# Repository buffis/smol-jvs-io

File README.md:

# smol-jvs-io

Smol JVS IO is a scoped down JVS I/O board designed to work as a drop-in replacement for arcade stick PCB's, to allow them to interface with JVS hardware. It is not meant to function as a fully functional JVS IO in terms of functionality.

This hardware and software of this board was forked from [td-io](https://github.com/tdaede/td-io) and then heavily scoped down to fit my needs. The td-io firmware is not directly compatible, due to design shortcuts on this board such as removing the shift registers.

At this point, I suppose not much of the td-io hardware schematic is used here any more. The firmware is still a pretty close fork though.

# Features

* JVS IO board interface as one-player device.
* Brook board compatible 20pin connector for hooking up player 1 stick and buttons.
* Upgradeable firmware

# BOM

Note that earlier versions may miss some of these, or have other component identifiers, but overall should be the same.

- U1 ADM3485EARZ-REEL7 or ST3485EBDR (or some other pin compatible one)
- U2 Raspberry Pi Pico
- Q1 AO3400A (Or any similar mosfet)
- D1 BAV99S,115 
- R1 0805 120ohm
- R2 0805 1k ohm
- J1 USBR-B-S-F-O-TH (Digikey: SAM10873-ND)
- J2 JST PH 1x4
- J3 JST PH 1x4
- J4 2.54mm Pinheader 2x10
- J5 JST XH 1x2

# Stuff intentionally not provided

* Player 2 controls
* Chaining other JVS IO boards
* Video/Audio handling
* Analog controls, Mahjong controls...

# Power

Power can either be provided to the micro USB port of the raspberry pi pico, or through the +5V/GND pins of the board.

# Firmware Updates

Flash the Raspberry Pi Pico with new firmware. Make sure stick is not powered from other sources.

# License

CERN-OHL-W

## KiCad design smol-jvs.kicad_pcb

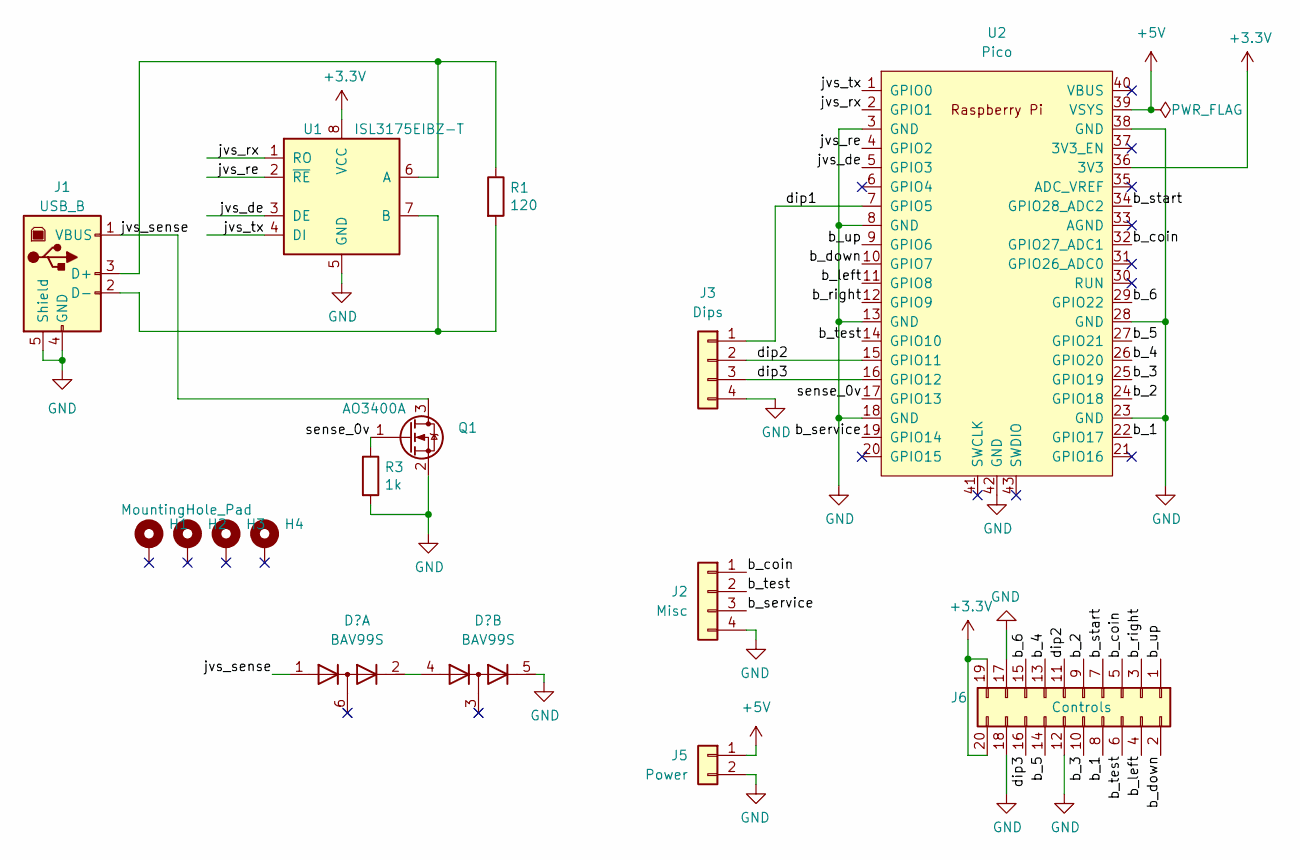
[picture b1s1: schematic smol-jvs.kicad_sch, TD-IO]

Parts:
H1, H2, H3, H4: MountingHole_Pad; MountingHole_2.5mm_Pad
J1: USB_B; USB_B_OST_USB-B1HSxx_Horizontal; Digikey SAM10873-ND
J2: Misc; JST_PH_B4B-PH-K_1x04_P2.00mm_Vertical
J3: Dips; JST_PH_B4B-PH-K_1x04_P2.00mm_Vertical
J5: Power; JST_XH_B2B-XH-AM_1x02_P2.50mm_Vertical
J6: Controls; PinHeader_2x10_P2.54mm_Vertical
Q1: AO3400A; SOT-23
R1: 120; R_0805_2012Metric; Digikey 13-RT0805FRE07120RLCT-ND
R3: 1k; R_0805_2012Metric; Digikey 311-10.0KCRCT-ND
U1: ISL3175EIBZ-T; SOIC-8_3.9x4.9mm_P1.27mm; Digikey 1016-1150-5-ND
U2: Pico; RPi_Pico_SMD_TH

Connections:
+3V3: J6.19, J6.20, U1.8 (VCC), U2.36 (3V3)
+5V: J5.1, U2.39 (VSYS)
/b_1: J6.8, U2.22 (GPIO17)
/b_2: J6.9, U2.24 (GPIO18)
/b_3: J6.10, U2.25 (GPIO19)
/b_4: J6.13, U2.26 (GPIO20)
/b_5: J6.14, U2.27 (GPIO21)
/b_6: J6.15, U2.29 (GPIO22)
/b_coin: J2.1, J6.5, U2.32 (GPIO27_ADC1)
/b_down: J6.2, U2.10 (GPIO7)
/b_left: J6.4, U2.11 (GPIO8)
/b_right: J6.3, U2.12 (GPIO9)
/b_service: J2.3, U2.19 (GPIO14)
/b_start: J6.7, U2.34 (GPIO28_ADC2)
/b_test: J2.2, J6.6, U2.14 (GPIO10)
/b_up: J6.1, U2.9 (GPIO6)
/dip1: J3.1, U2.7 (GPIO5)
/dip2: J3.2, J6.11, U2.15 (GPIO11)
/dip3: J3.3, J6.16, U2.16 (GPIO12)
/jvs_de: U1.3 (DE), U2.5 (GPIO3)
/jvs_re: U1.2 (~RE), U2.4 (GPIO2)
/jvs_rx: U1.1 (RO), U2.2 (GPIO1)
/jvs_sense: J1.1 (VBUS), Q1.3 (D); also elsewhere on the board
/jvs_tx: U1.4 (DI), U2.1 (GPIO0)
/sense_0v: Q1.1 (G), R3.1, U2.17 (GPIO13)
GND: J1.4 (GND), J1.5 (Shield), J2.4, J3.4, J5.2, J6.12, J6.17, J6.18, Q1.2 (S), R3.2, U1.5 (GND), U2.3 (GND), U2.8 (GND), U2.13 (GND), U2.18 (GND), U2.23 (GND), U2.28 (GND), U2.38 (GND), U2.42 (GND); also elsewhere on the board
unnamed: J1.2 (D-), R1.2, U1.7 (B)
unnamed: J1.3 (D+), R1.1, U1.6 (A)

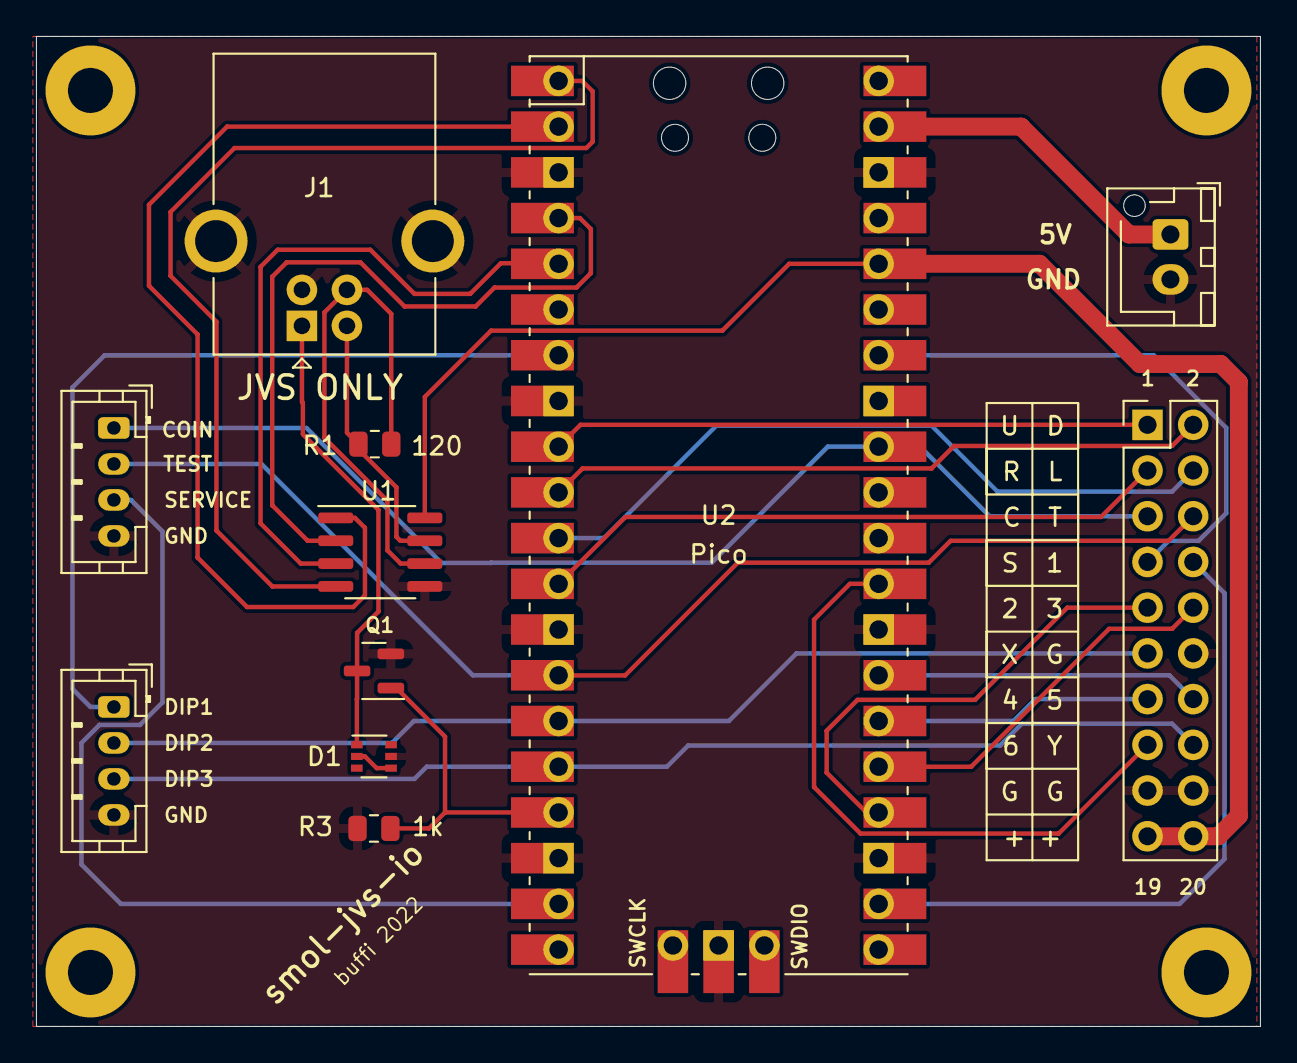
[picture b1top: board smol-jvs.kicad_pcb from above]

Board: 2 copper layers, 68.0 x 55.0 mm, 15 parts (0 on the bottom side), 29 nets.

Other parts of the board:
D1: BAV99S; SOT-363_SC-70-6

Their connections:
/jvs_sense: D1.1 (A1); also elsewhere on the board
GND: D1.5 (K4); also elsewhere on the board
unnamed: D1.2 (K2), D1.4 (A3)

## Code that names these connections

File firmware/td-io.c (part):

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#include "hardware/adc.h"
#include <string.h>

const uint PIN_JVS_RE = 2;
const uint PIN_JVS_DE = 3;

const uint PIN_JVS_SENSE_0V = 13;

const uint PIN_JVS_TERMINATION = 15; // TODO: Remove.

const uint PIN_LED_ENUMERATED = PICO_DEFAULT_LED_PIN;
const uint PIN_DIP1 = 11;
const uint PIN_DIP2 = 12;
const uint PIN_DIP3 = 15;

// New pins for direct inputs.
const uint PIN_BTN_TEST = 10;
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}

void start_transmit() {
    gpio_put(PIN_JVS_RE, 1); // disable receive
    busy_wait_us_32(200);    // 200us min for exa compat
    gpio_put(PIN_JVS_DE, 1); // enable transmitter
}

void stop_transmit() {
    uart_tx_wait_blocking(uart0);
    gpio_put(PIN_JVS_DE, 0); // disable transmitter
    gpio_put(PIN_JVS_RE, 0); // enable receiver
}

void send_message(uint8_t status, uint8_t* m, uint8_t msg_len) {
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    uart_set_translate_crlf(uart0, false);
    gpio_set_function(0, GPIO_FUNC_UART);
    gpio_set_function(1, GPIO_FUNC_UART);
    gpio_init(PIN_JVS_RE);
    gpio_put(PIN_JVS_RE, 0); // enable receiver
    gpio_set_dir(PIN_JVS_RE, GPIO_OUT);
    gpio_init(PIN_JVS_DE);
    gpio_put(PIN_JVS_DE, 0); //disable transmitter
    gpio_set_dir(PIN_JVS_DE, GPIO_OUT);
    gpio_init(PIN_JVS_SENSE_0V);
    gpio_put(PIN_JVS_SENSE_0V, 0);
    gpio_set_dir(PIN_JVS_SENSE_0V, GPIO_OUT);
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    gpio_init(PIN_LED_ENUMERATED);
    gpio_put(PIN_LED_ENUMERATED, 0);
    gpio_set_dir(PIN_LED_ENUMERATED, GPIO_OUT);
    gpio_init(PIN_DIP1);
    gpio_set_dir(PIN_DIP1, GPIO_IN);
    gpio_pull_up(PIN_DIP1);

    // Control inputs
    gpio_init(PIN_BTN_TEST);
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                        printf("Got input descriptor request\n");
                        msg_send[o] = JVS_REPORT_GOOD;
                        o++;
                        if (!gpio_get(PIN_DIP1)) {
                            memcpy(&msg_send[o], input_desc_1coin, sizeof(input_desc_1coin));
                            o += sizeof(input_desc_1coin);
                        } else {
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
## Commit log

2022-09-19 Cleaned up pcb
2022-09-19 Gerbers
2022-09-19 Minor fixes
2022-09-20 Minor cleanup
2022-10-07 many minor changes
2022-10-08 misc stuff
2022-10-08 rename to smol-jvs
2022-10-08 cleanup
2022-10-08 Fix name of IO
2022-10-09 New gerbers
2022-10-12 new gerbers and minor updates
2022-11-08 Go back to using diodes for sense again
2023-02-06 Minor pcb updates + BOM
